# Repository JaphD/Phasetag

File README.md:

# PhaseTag

PhaseTag is a compact, rechargeable Bluetooth Channel Sounding tag designed around the Nordic nRF54L15. It brings together two selectable PCB antennas, motion sensing and USB-C charging on a **35 x 42.5 mm, four-layer PCB** designed with JLCPCB manufacturing and assembly in mind.

The aim is to explore wireless distance estimation with a compatible Channel Sounding peer and report results over BLE to a suitable host application. Motion sensing provides a basis for activity detection and low-power operation.

**Rev A is a hardware portfolio design.** Firmware, physical bring-up, antenna tuning, ranging accuracy and battery life have not been validated. The images below are KiCad renders and a PCB editor view.

## Board preview

| Top view | Bottom view |
| --- | --- |
|  |  |

### PCB layout

## Main hardware

| Block | Implementation |
| --- | --- |
| MCU and radio | Nordic nRF54L15-QFAA with 32 MHz and 32.768 kHz crystals |
| Power management | Nordic nPM1300 for single-cell LiPo charging, USB/battery power-path management and the 1.8 V rail |
| RF path | Nordic matching network, BGS12WN6 antenna switch and two perpendicular TI AN043 PCB inverted-F antennas |
| Motion sensing | ST LIS2DW12 accelerometer with an interrupt connection to the MCU |
| Power inputs | Power-only USB-C with VBUS ESD protection; 2 mm JST-PH battery connector with reverse-polarity protection |
| User interface | PMIC-controlled status LED and SHPHLD wake/recovery button |
| Programming | Six-pad Tag-Connect SWD/SWO interface, reset and target-voltage reference |
| Test access | Ground, battery, VSYS, 1.8 V, SDA and SCL test pads |

## Design choices

### Power and battery

BUCK1 supplies the 1.8 V MCU and peripheral rail. BUCK2 and both load-switch/LDO outputs are unused to keep the power circuit small. The nPM1300 allows USB to power the system while charging the battery, subject to the available input-current and power budgets. The PMIC and accelerometer share a 1.8 V I2C bus with one pair of 4.7 kohm pull-ups.

The battery sits separately from the PCB. A PKCELL LP402535, 3.7 V, 330 mAh LiPo is a candidate rather than a fixed requirement. The reverse-polarity circuit follows the approach in Analog Devices AN171, Figure 4, accommodating charging and discharge current. Battery polarity and charging limits must match the chosen pack.

Battery NTC sensing is omitted in this revision. Firmware must configure the PMIC accordingly and set the charging current, termination voltage and USB input-current limit. PMIC measurements support battery monitoring; a useful remaining-capacity estimate also requires appropriate firmware and battery characterization.

### RF and antenna selection

The MCU supply, oscillator and matching circuitry use the Nordic nRF54L15-QFAA Configuration 1 reference as their baseline. The RF switch selects one antenna at a time. The perpendicular antennas provide different orientations for evaluation; they do not operate as a combined antenna array.

Both antenna paths retain pi-matching footprints. R9 and R10 are fitted as 0-ohm links, while C27 through C30 are unpopulated. These footprints preserve tuning options for a future prototype. The TI antenna geometry is a reference starting point; copying its shape does not establish the final board's RF performance.

The nominal 50-ohm top-layer feed width retained in the design is 0.18379 mm, referenced to the adjacent inner ground layer. This target depends on the selected stackup and surrounding copper. It has not been verified by measurement.

### Compact construction and access

All components are populated on the top side. Tag-Connect programming pads avoid a fitted debug header, and the separate battery helps minimize the board area. One M2 mounting hole is provided, with a future enclosure expected to provide a second support and prevent rotation.

USB-C carries power only. Bluetooth is the intended application-data interface. Channel Sounding needs a compatible peer; ordinary BLE support alone does not make a phone suitable for ranging. Bluetooth Mesh remains a possible future firmware application.

## JLCPCB manufacturing and assembly

The fabrication target is nominal **1.6 mm, four-layer FR-4**, based on the **JLC04161H-3313** stackup:

| Layer | Purpose |
| --- | --- |
| F.Cu | Components, RF paths and signal/power routing |
| In1.Cu | Main ground reference |
| In2.Cu | Limited power routing and ground fill |
| B.Cu | Remaining signals and ground fill |

- Component selection uses JLCPCB/LCSC part numbers. Small packages, including 0201 passives, and Extended parts are accepted design tradeoffs. Stock, substitutes and assembly-service eligibility need checking when ordering.
- The **16 vias beneath the nRF exposed pad require epoxy filling and copper capping**. Identify these vias explicitly in the fabrication order; the KiCad protection settings alone are insufficient manufacturing instructions.
- Preserve the antenna keepouts and RF ground arrangement. A change in stackup requires the feed geometry to be checked again.
- Manufacturing outputs comprise Gerbers, drills, a BOM and a CPL/position file. Verify package, polarity, rotation and matching designators. Exclude DNP parts, PCB antennas, test pads, the mounting hole and logo from fitted-component data.

The reference basis also includes Nordic's nPM1300 Configuration 2 circuit, adapted for the selected power architecture, and the ST LIS2DW12 datasheet. These references inform the design; they do not replace prototype validation.

## Opening the project

Open [Bluetooth_Channel_Sounding_Tag.kicad_pro](Bluetooth_Channel_Sounding_Tag.kicad_pro) in **KiCad 10**.

- The project files contain the schematic, board and design rules.
- `Lib/` contains the imported symbols, footprints and 3D models, referenced through the project library tables. Imported absolute 3D-model paths may need remapping to this directory on another computer.
- `logo/` contains the PhaseTag logo artwork and footprint.
- `images/` contains the board renders and layout screenshot used above.

Designed by **Yafet Daniel**.

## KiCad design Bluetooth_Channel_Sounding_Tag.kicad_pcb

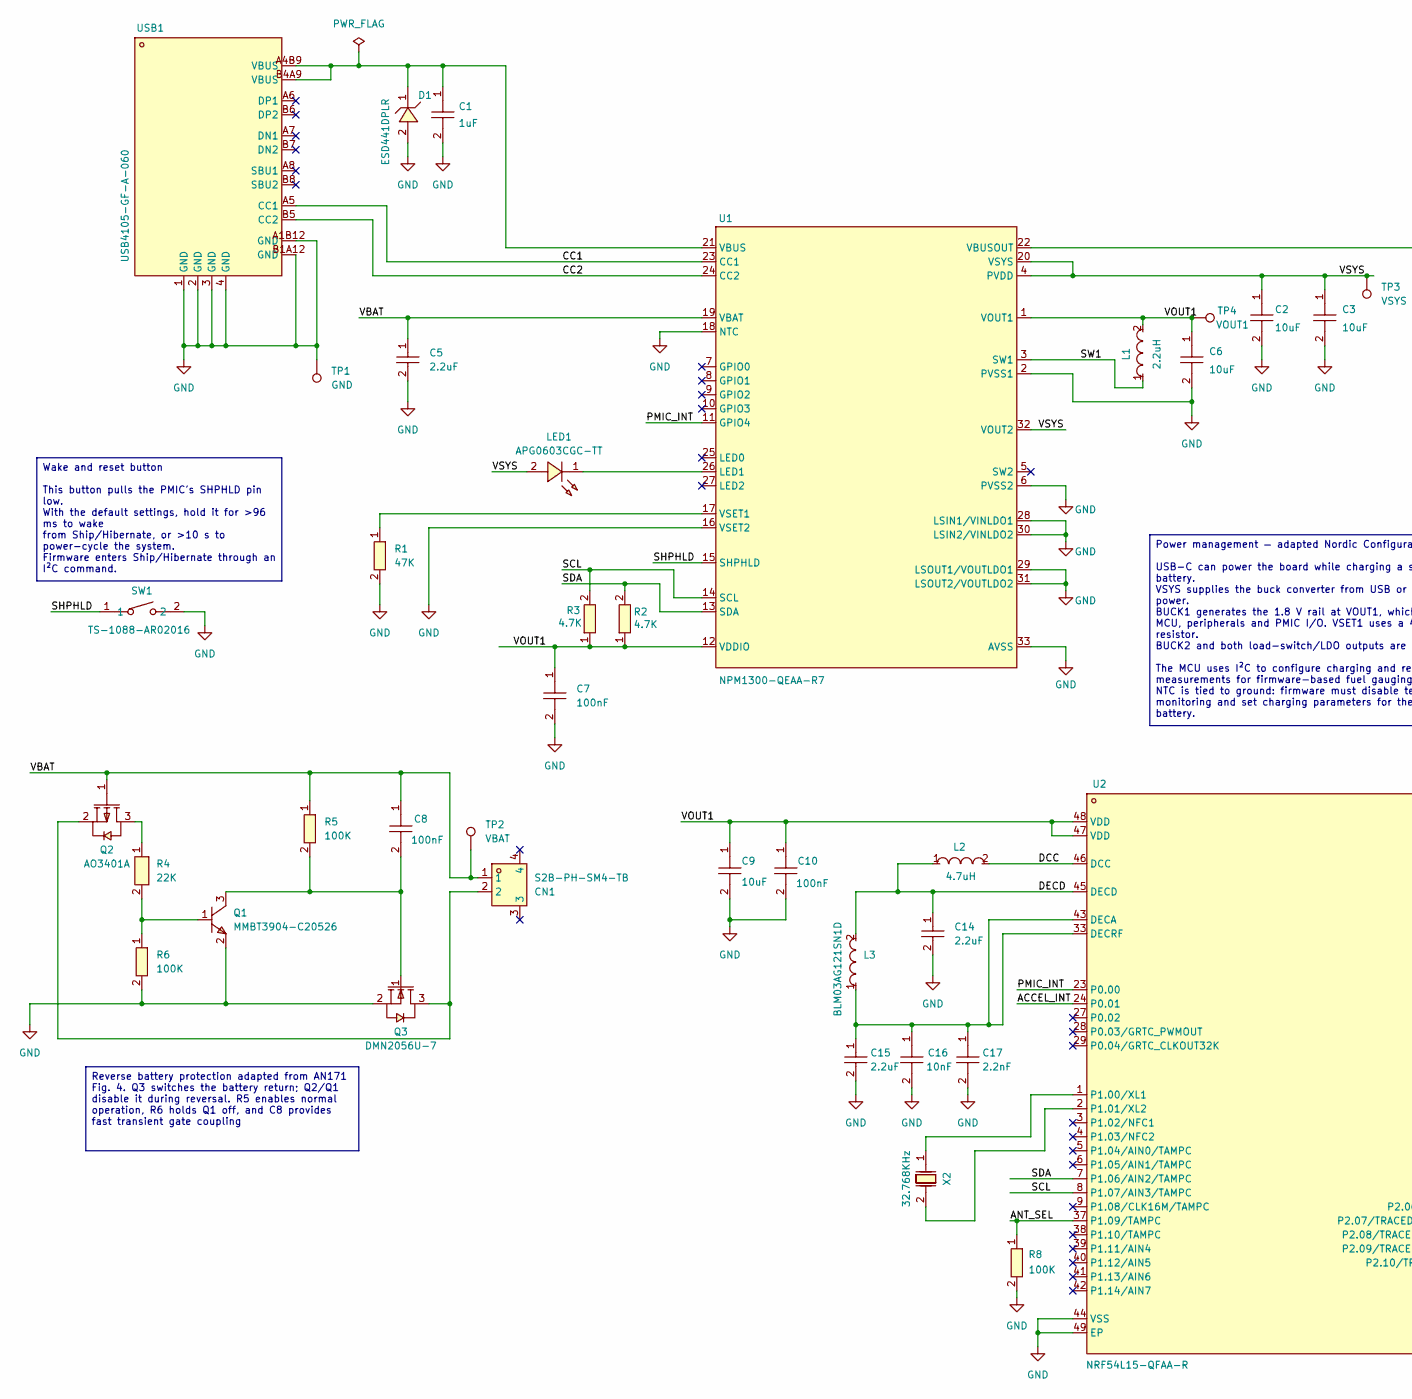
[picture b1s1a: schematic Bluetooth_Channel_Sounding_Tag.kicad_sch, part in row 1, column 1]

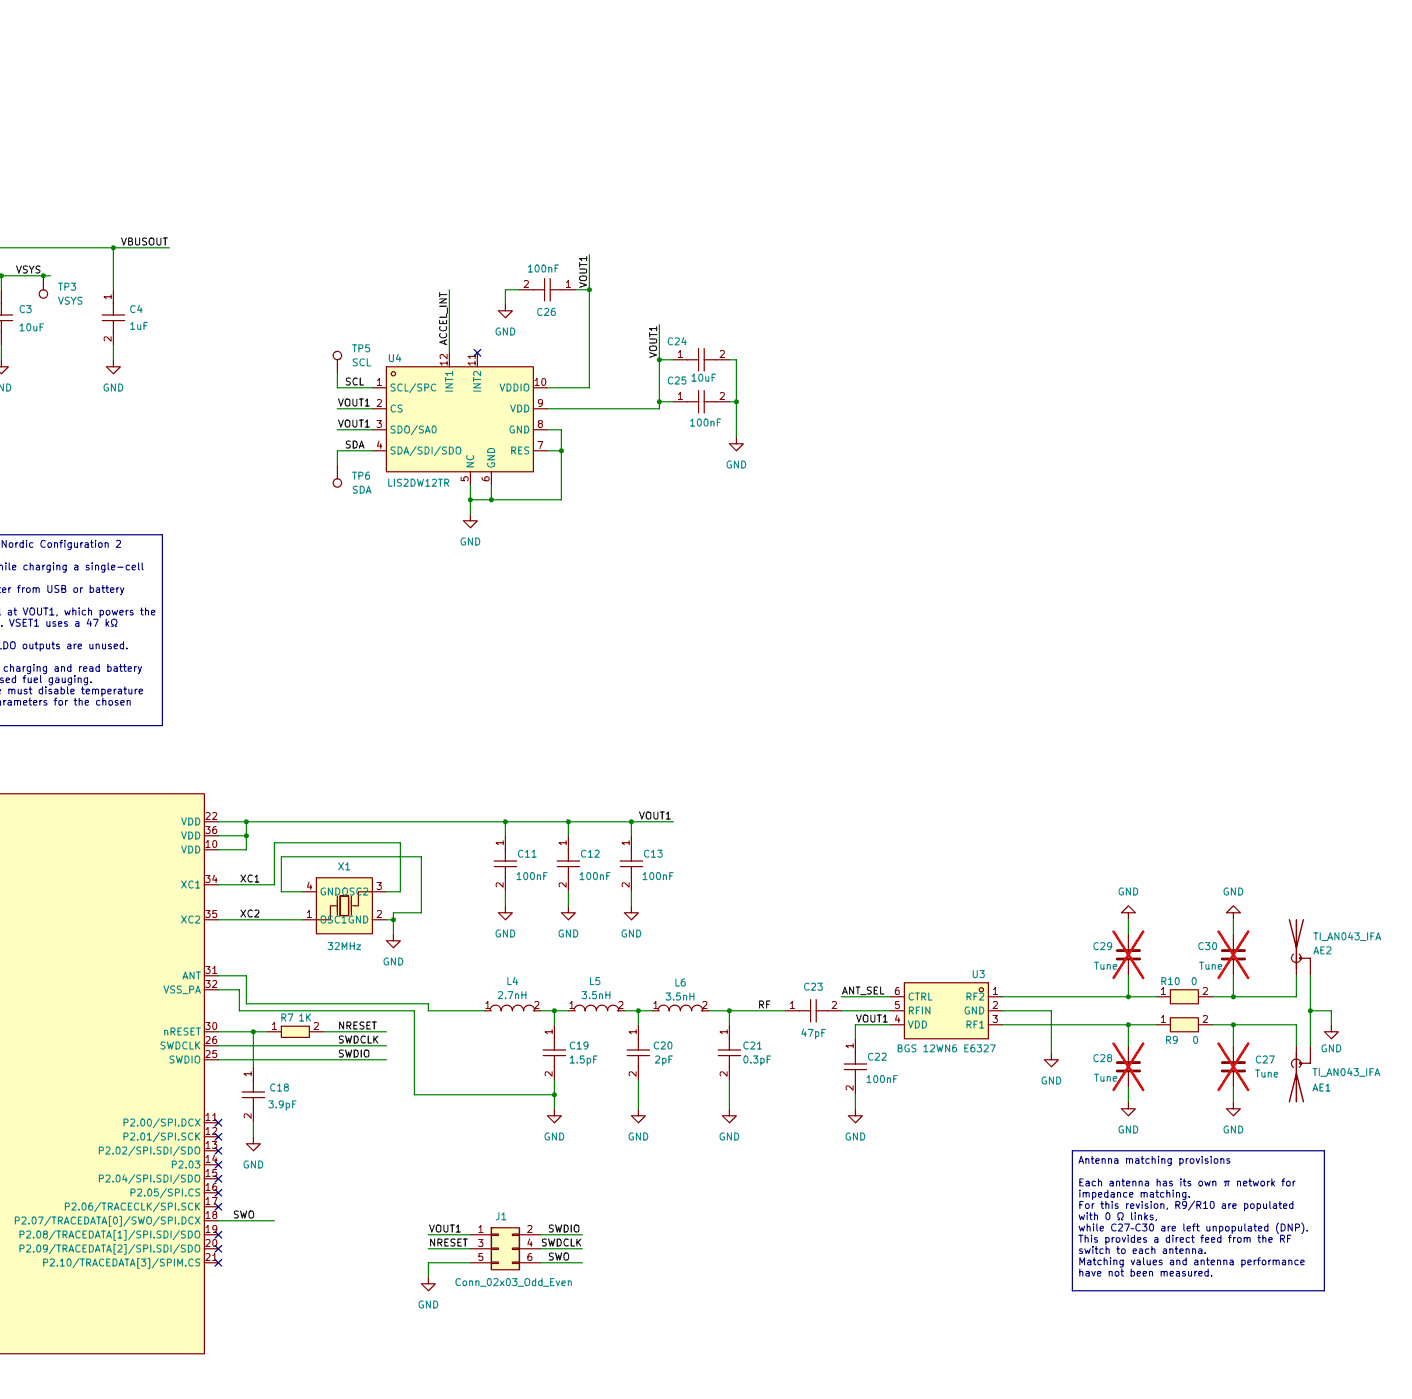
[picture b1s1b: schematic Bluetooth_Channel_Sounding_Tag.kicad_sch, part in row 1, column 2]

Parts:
AE1: TI_AN043_IFA; Texas_SWRA117D_2.4GHz_Left
AE2: TI_AN043_IFA; Texas_SWRA117D_2.4GHz_Right
C1, C4: 1uF; C0603; MPN CL10A105KB8NNNC; LCSC Part C15849
C2, C3, C6, C24: 10uF; C0603; MPN CL10A106MA8NRNC; LCSC Part C96446
C5: 2.2uF; C0603; MPN CL10A225KO8NNNC; LCSC Part C23630
C7, C10, C11, C12, C13, C22, C25, C26: 100nF; C0201; MPN CL03A104KP3NNNC; LCSC Part C49062
C8: 100nF; C0402; MPN CL05B104KB54PNC; LCSC Part C307331
C9: 10uF; C0402; MPN GRM155R61A106ME11D; LCSC Part C408132
C14, C15: 2.2uF; C0201; MPN GRM033R60J225ME47D; LCSC Part C76933
C16: 10nF; C0201; MPN CC0201KRX7R7BB103; LCSC Part C272853
C17: 2.2nF; C0201; MPN 0201B222K160NT; LCSC Part C284975
C18: 3.9pF; C0201; MPN TCC0201COG3R9C500ZT; LCSC Part C18164580
C19: 1.5pF; C0201; MPN GJM0335C1E1R5WB01D; LCSC Part C435397
C20: 2pF; C0201; MPN GJM0335C1E2R0WB01D; LCSC Part C668326
C21: 0.3pF; C0201; MPN GJM0335C1ER30WB01D; LCSC Part C161289
C23: 47pF; C0201; MPN GRM0335C1H470JA01D; LCSC Part C85908
C27, C28, C29, C30: Tune; C0201; not fitted
CN1: S2B-PH-SM4-TB; CONN-SMD_P2.00_S2B-PH-SM4-TB-LF-SN; MPN S2B-PH-SM4-TB(LF)(SN); LCSC Part C295747
D1: ESD441DPLR; X2SON-2_L0.6-W0.3-P0.35; MPN ESD441DPLR; LCSC Part C22427765
J1: Conn_02x03_Odd_Even; Tag-Connect_TC2030-IDC-NL_2x03_P1.27mm_Vertical
L1: 2.2uH; L0805; MPN MLP2012S2R2MT0S1; LCSC Part C107322
L2: 4.7uH; L0603; MPN MLZ1608M4R7WT000; LCSC Part C76799
L3: BLM03AG121SN1D; L0201; MPN BLM03AG121SN1D; LCSC Part C97850
L4: 2.7nH; L0201; MPN LQP03HQ2N7B02D; LCSC Part C7216765
L5, L6: 3.5nH; L0201; MPN LQP03HQ3N5B02D; LCSC Part C3911055
LED1: APG0603CGC-TT; LED-SMD_L0.7-W0.4-RD_GREEN-1; MPN APG0603CGC-TT; LCSC Part C4153580
Q1: MMBT3904-C20526; SOT-23-3_L2.9-W1.3-P1.90-LS2.4-BR; MPN MMBT3904(RANGE:100-300); LCSC Part C20526
Q2: AO3401A; SOT-23_L2.9-W1.3-P1.90-LS2.4-BR; MPN AO3401A; LCSC Part C15127
Q3: DMN2056U-7; SOT-23-3_L2.9-W1.6-P1.90-LS2.8-BR; MPN DMN2056U-7; LCSC Part C332302
R1: 47K; R0201; MPN 0201WMF4702TEE; LCSC Part C270345
R2, R3: 4.7K; R0201; MPN RC0201FR-074K7L; LCSC Part C138135
R4: 22K; R0201; MPN RC0201FR-0722KL; LCSC Part C474416
R5, R6, R8: 100K; R0201; MPN RC0201FR-07100KL; LCSC Part C106224
R7: 1K; R0201; MPN 0201WMF1001TEE; LCSC Part C270365
R9, R10: 0; R0201; MPN 0201WMF0000TEE; LCSC Part C473473
SW1: TS-1088-AR02016; SW-SMD_L3.9-W3.0-P4.45; MPN TS-1088-AR02016; LCSC Part C720477
TP1: GND; TestPoint_Pad_D1.0mm
TP2: VBAT; TestPoint_Pad_D1.0mm
TP3: VSYS; TestPoint_Pad_D1.0mm
TP4: VOUT1; TestPoint_Pad_D1.0mm
TP5: SCL; TestPoint_Pad_D1.0mm
TP6: SDA; TestPoint_Pad_D1.0mm
U1: NPM1300-QEAA-R7; QFN-32_L5.0-W5.0-P0.50-TL-EP3.5; MPN nPM1300-QEAA-R7; LCSC Part C7501206
U2: NRF54L15-QFAA-R; QFN-48_L6.0-W6.0-P0.40-TL-EP4.6; MPN NRF54L15-QFAA-R; LCSC Part C42458750
U3: BGS 12WN6 E6327; TSNP-6_L1.1-W0.7-P0.40-BL; MPN BGS 12WN6 E6327; LCSC Part C534203
U4: LIS2DW12TR; LGA-12_L2.0-W2.0-P0.50-BL; MPN LIS2DW12TR; LCSC Part C189624
USB1: USB4105-GF-A-060; USB-C-SMD_GT-USB-7010E-1; MPN USB4105-GF-A-060; LCSC Part C3025063
X1: 32MHz; CRYSTAL-SMD_4P-L2.0-W1.6-BL; MPN ABM11W-32.0000MHZ-8-B1U-T3; LCSC Part C1985774
X2: 32.768KHz; CRYSTAL-SMD_L2.0-W1.2; MPN CM8V-T1A-32.768kHz-9pF-20PPM-TB-QC; LCSC Part C5280691

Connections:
/ACCEL_INT: U2.24 (P0.01), U4.12 (INT1)
/ANT_SEL: R8.1, U2.37 (P1.09/TAMPC), U3.6 (CTRL)
/CC1: U1.23 (CC1), USB1.A5 (CC1)
/CC2: U1.24 (CC2), USB1.B5 (CC2)
/DCC: L2.2, U2.46 (DCC)
/DECD: C14.1, L2.1, L3.2, U2.45 (DECD)
/NRESET: J1.3, R7.2
/PMIC_INT: U1.11 (GPIO4), U2.23 (P0.00)
/RF: C21.1, C23.1, L6.2
/SCL: R3.2, TP5.1 (1_1), U1.14 (SCL), U2.8 (P1.07/AIN3/TAMPC), U4.1 (SCL/SPC)
/SDA: R2.2, TP6.1 (1_1), U1.13 (SDA), U2.7 (P1.06/AIN2/TAMPC), U4.4 (SDA/SDI/SDO)
/SHPHLD: SW1.1, U1.15 (SHPHLD)
/SW1: L1.1, U1.3 (SW1)
/SWDCLK: J1.4, U2.26 (SWDCLK)
/SWDIO: J1.2, U2.25 (SWDIO)
/SWO: J1.6, U2.18 (P2.07/TRACEDATA[0]/SWO/SPI.DCX)
/VBAT: C5.1, C8.1, CN1.1, Q2.1, R5.1, TP2.1 (1_1), U1.19 (VBAT)
/VBUSOUT: C4.1, U1.22 (VBUSOUT)
/VOUT1: C6.1, C7.1, C9.1, C10.1, C11.1, C12.1, C13.1, C22.1, C24.1, C25.1, C26.1, J1.1, L1.2, R2.1, R3.1, TP4.1 (1_1), U1.1 (VOUT1), U1.12 (VDDIO), U2.10 (VDD), U2.22 (VDD), U2.36 (VDD), U2.47 (VDD), U2.48 (VDD), U3.4 (VDD), U4.2 (CS), U4.3 (SDO/SA0), U4.9 (VDD), U4.10 (VDDIO)
/VSYS: C2.1, C3.1, LED1.2, TP3.1 (1_1), U1.4 (PVDD), U1.20 (VSYS), U1.32 (VOUT2)
/XC1: U2.34 (XC1), X1.3 (OSC2)
/XC2: U2.35 (XC2), X1.1 (OSC1)
GND: AE1.2 (Shield), AE2.2 (Shield), C1.2, C2.2, C3.2, C4.2, C5.2, C6.2, C7.2, C9.2, C10.2, C11.2, C12.2, C13.2, C14.2, C15.2, C16.2, C17.2, C18.2, C19.2, C20.2, C21.2, C22.2, C24.2, C25.2, C26.2, C27.2, C28.2, C29.1, C30.1, D1.2, J1.5, Q1.2, Q3.2, R1.2, R6.2, R8.2, SW1.2, TP1.1 (1_1), U1.2 (PVSS1), U1.6 (PVSS2), U1.16 (VSET2), U1.18 (NTC), U1.28 (LSIN1/VINLDO1), U1.29 (LSOUT1/VOUTLDO1), U1.30 (LSIN2/VINLDO2), U1.31 (LSOUT2/VOUTLDO2), U1.33 (AVSS), U2.32 (VSS_PA), U2.44 (VSS), U2.49 (EP), U3.2 (GND), U4.5 (NC), U4.6 (GND), U4.7 (RES), U4.8 (GND), USB1.1 (GND), USB1.2 (GND), USB1.3 (GND), USB1.4 (GND), USB1.A1B12 (GND), USB1.B1A12 (GND), X1.2 (GND), X1.4 (GND)
unnamed: AE1.1 (A), C27.1, R9.2
unnamed: AE2.1 (A), C30.2, R10.2
unnamed: C8.2, Q1.3, Q3.1, R5.2
unnamed: C19.1, L4.2, L5.1
unnamed: C20.1, L5.2, L6.1
unnamed: CN1.2, Q2.2, Q3.3
unnamed: Q1.1, R4.2, R6.1
unnamed: Q2.3, R4.1
unnamed: LED1.1, U1.26 (LED1)
unnamed: C1.1, D1.1, U1.21 (VBUS), USB1.A4B9 (VBUS), USB1.B4A9 (VBUS)
unnamed: R1.1, U1.17 (VSET1)
unnamed: L4.1, U2.31 (ANT)
unnamed: C15.1, C16.1, C17.1, L3.1, U2.33 (DECRF), U2.43 (DECA)
unnamed: U2.1 (P1.00/XL1), X2.1
unnamed: U2.2 (P1.01/XL2), X2.2
unnamed: C18.1, R7.1, U2.30 (nRESET)
unnamed: C28.1, R9.1, U3.3 (RF1)
unnamed: C29.2, R10.1, U3.1 (RF2)
unnamed: C23.2, U3.5 (RFIN)

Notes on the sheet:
Reverse battery protection adapted from AN171 Fig. 4. Q3 switches the battery return; Q2/Q1 disable it during reversal. R5 enables normal operation, R6 holds Q1 off, and C8 provides fast transient gate coupling
Power management — adapted Nordic Configuration 2 USB-C can power the board while charging a single-cell battery. VSYS supplies the buck converter from USB or battery power. BUCK1 generates the 1.8 V rail at VOUT1, which powers the MCU, peripherals and PMIC I/O. VSET1 uses a 47 kΩ resistor. BUCK2 a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
Antenna matching provisions Each antenna has its own π network for impedance matching. For this revision, R9/R10 are populated with 0 Ω links, while C27–C30 are left unpopulated (DNP). This provides a direct feed from the RF switch to each antenna. Matching values and antenna performance have not b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
Wake and reset button This button pulls the PMIC's SHPHLD pin low. With the default settings, hold it for >96 ms to wake from Ship/Hibernate, or >10 s to power-cycle the system. Firmware enters Ship/Hibernate through an I²C command.

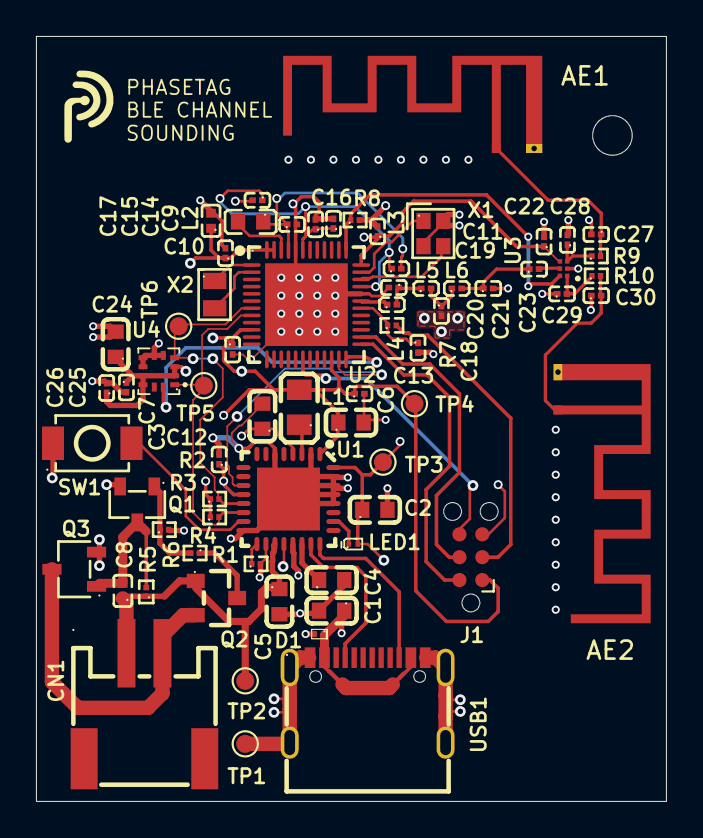
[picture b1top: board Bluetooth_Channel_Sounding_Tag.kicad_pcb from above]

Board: 4 copper layers, 35.0 x 42.5 mm, 70 parts (0 on the bottom side), 42 nets.

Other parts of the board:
H1: MountingHole_2.2mm_M2
